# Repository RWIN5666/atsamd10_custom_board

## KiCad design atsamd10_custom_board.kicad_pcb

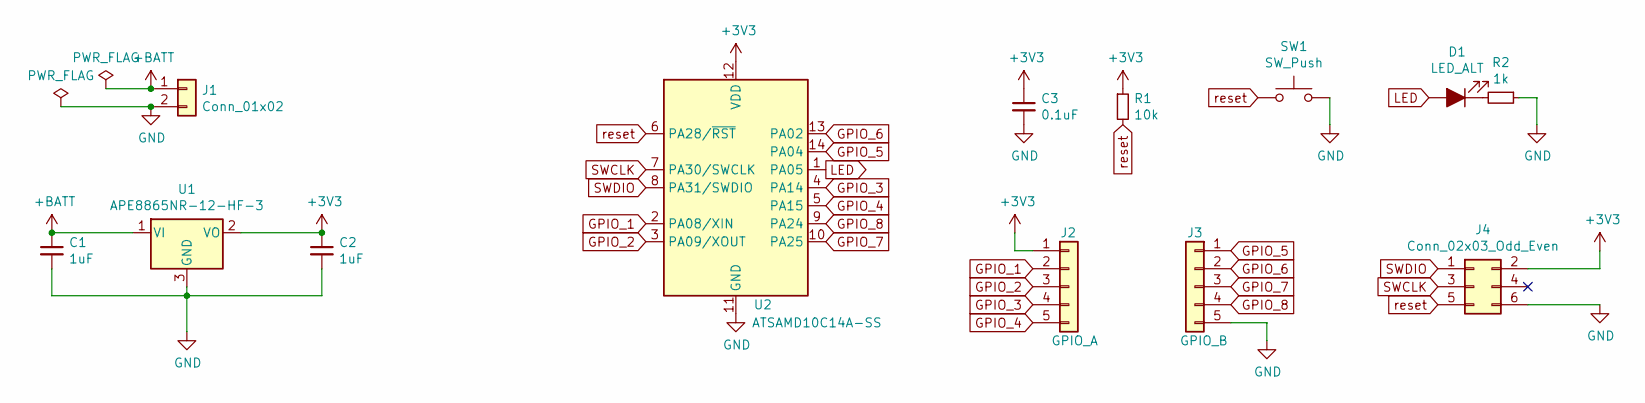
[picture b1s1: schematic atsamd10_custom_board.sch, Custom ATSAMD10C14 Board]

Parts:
C1, C2: 1uF; C_0603_HandSoldering
C3: 0.1uF; C_0603_HandSoldering
D1: LED_ALT; LED_0603_HandSoldering
J1: Conn_01x02; JST_PH_B2B-PH-K_02x2.00mm_Straight
J2: GPIO_A; Pin_Header_Straight_1x05_Pitch2.54mm
J3: GPIO_B; Pin_Header_Straight_1x05_Pitch2.54mm
J4: Conn_02x03_Odd_Even; Pin_Header_Straight_2x03_Pitch2.54mm
R1: 10k; R_0603_HandSoldering
R2: 1k; R_0603_HandSoldering
SW1: SW_Push; SW_PUSH_6mm
U1: APE8865NR-12-HF-3; SOT-23
U2: ATSAMD10C14A-SS; SOIC-14_3.9x8.7mm_P1.27mm

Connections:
+3V3: C2.1, C3.1, J2.1, J4.2, R1.1, U1.2 (VO), U2.12 (VDD)
+BATT: C1.1, J1.1, U1.1 (VI)
GND: C1.2, C2.2, C3.2, J1.2, J3.5, J4.6, R2.1, SW1.2, U1.3 (GND), U2.11 (GND)
GPIO_1: J2.2, U2.2 (PA08/XIN)
GPIO_2: J2.3, U2.3 (PA09/XOUT)
GPIO_3: J2.4, U2.4 (PA14)
GPIO_4: J2.5, U2.5 (PA15)
GPIO_5: J3.1, U2.14 (PA04)
GPIO_6: J3.2, U2.13 (PA02)
GPIO_7: J3.3, U2.10 (PA25)
GPIO_8: J3.4, U2.9 (PA24)
LED: D1.2 (A), U2.1 (PA05)
unnamed: D1.1 (K), R2.2
SWCLK: J4.3, U2.7 (PA30/SWCLK)
SWDIO: J4.1, U2.8 (PA31/SWDIO)
reset: J4.5, R1.2, SW1.1, U2.6 (PA28/~RST)

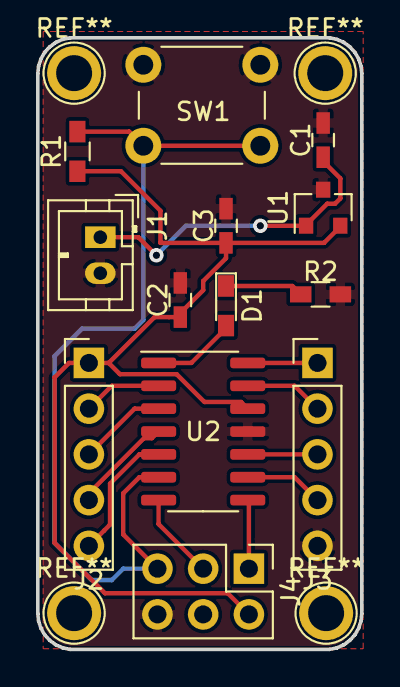
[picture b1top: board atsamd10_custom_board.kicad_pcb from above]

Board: 2 copper layers, 18.0 x 34.0 mm, 13 parts (0 on the bottom side), 16 nets.

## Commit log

2019-08-01 Initial Commit.
    Custom board in order to prepare a new project.
